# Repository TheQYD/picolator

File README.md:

## Picolator
A portable console for [Pico 8] (http://www.lexaloffle.com/pico-8.php).   

## Details
Picolator is a portable console developed using the Raspberry Pi Zero. It's shell and circuits are made using the [Othermill](https://othermachine.co). 

Anyone with experience in milling and circuit design should be able to make it from just the files. I'll put together an Instructable soon. Check the notes for design details.

## Parts
- 1 [Raspberry Zero] (https://www.adafruit.com/product/2885)
- 1 [Teensy 3.2] (https://www.pjrc.com/store/teensy32.html)
- 1 [Adafruit 3.5” PiTFT] (https://www.adafruit.com/products/2097)
- 1 [LM386 Audio Amplifier] (http://www.digikey.com/product-detail/en/texas-instruments/LM386N-4-NOPB/296-43960-5-ND/148192)
- 1 [Adafruit PowerBoost 500c] (https://www.adafruit.com/product/1944)
- 1 [3.7v 2500mAh LiPo battery] (https://www.adafruit.com/products/328)
- 1 [2.5mm headphone jack] (https://www.amazon.com/uxcell-Plastic-Stereo-Socket-Connector/dp/B00GLQAF7A/ref=pd_sim_23_4/151-6327110-2786334?_encoding=UTF8&pd_rd_i=B00GLQAF7A&pd_rd_r=0DZXJB3YZX57Q64PYSKV&pd_rd_w=IB4NA&pd_rd_wg=bLT86&psc=1&refRID=0DZXJB3YZX57Q64PYSKV)
- 1 [sheet of 4” x 3” x .375” polycarbonate] (https://othermachine.co/store/materials/polycarbonate/)
- 2 [sheets of 4” x 3” x .375” HDPE] (https://othermachine.co/store/materials/hdpe/)
- 1 [sheet of 4” x 3” copper clad FR-1](https://othermachine.co/store/materials/pcb)
- Misc: resistors, capacitors, switch, etc.

## Media
A video it it in action can be found [here](https://youtu.be/5mOcTelc-4U).

The front.

The back.

I use it all the time.

Here are it's insides. I was breadboarding it.

This is the soundboard. It uses an LM386. I designed this circuit for the console, but the Pi Zero audio output instructions can be found [here](https://learn.adafruit.com/introducing-the-raspberry-pi-zero/audio-outputs). It's based on that.

The schematic for the soundboard is in the CADs folder, but here's an image of it.

This is the controller. It connects to the Teensy and the Teensy is then connected via USB to the Pi Zero.

This is a screenshot of the controller circuit. It's also in the CADs folder.

## Notes
The shell is 4 layers. Three HDPE layers and a polycarbonate top layer (to protect the screen). The body was designed in Fusion 360, and the electronics were designed in EagleCAD. All of them were milled using the Othermill. I had to use a Dremel to remove the headers on the PiTFT (risky, but it needed to be thinner). It's not hollow, there are supports and channels to route the wires and mount equipment on the inside (see the CADs).

When I started, I found the PiTFT schematic and tested the pins used for video (SPI). The wires are 28 gauge stranded core. If you look through Google Images for any of those things you'd need, you'll find them. Lady Ada makes the schematics for the PiTFT available on her site. The mappings I found in Google images, and tested using an oscilliscope.

The joystick is milled in two parts. The section for the screen is located in the cads/body directory. The circuit is located in the body/circuits directory. The resistors are 10k pullups. The Teensy code has a mapping of the pins, which are also labeled on the schematic.

The image is Lady Ada's PiTFT image (Raspbian), so the SD Card is 8GB. I couldn't get it booting when I used dd on a 32GB card. If anyone knows why, send me message -- though I don't think that's necessary even if I had every Pico-8 game ever. The games are played in Pico-8. You can place the flags in rc.local so it starts automatically. Pico 8 is available from [Lexaloffle Games](http://www.lexaloffle.com/pico-8.php). All of the games are made by the community using Lua (I guess I'm about to learn Lua!). 

That's it for now, until I have time to write an Instructable.

## License
Picolator is available under the MIT license. See the LICENSE file for more info. Make it better!

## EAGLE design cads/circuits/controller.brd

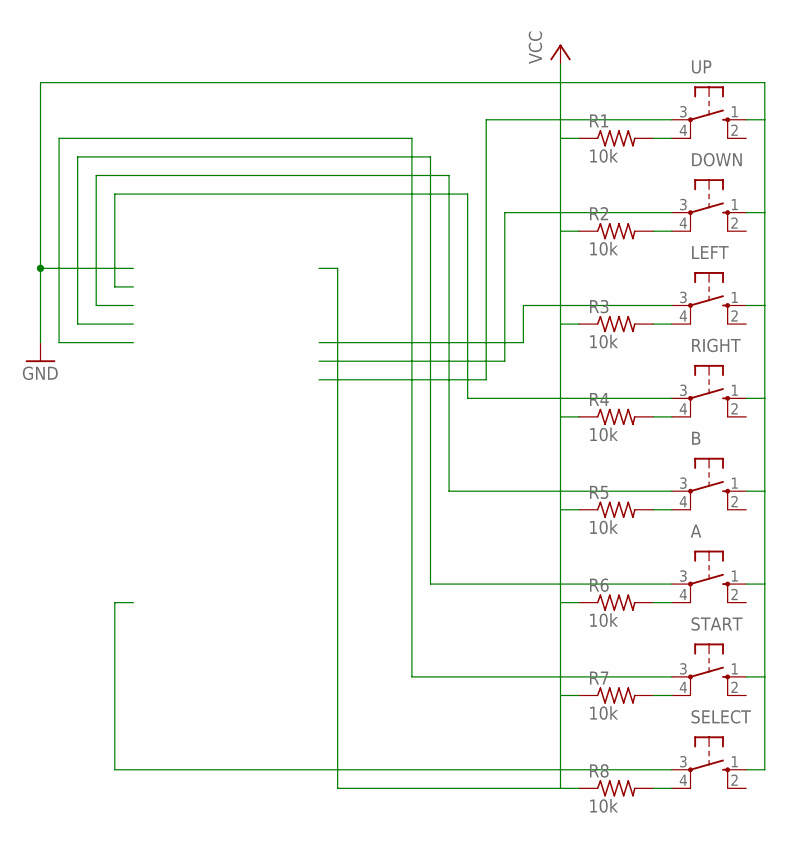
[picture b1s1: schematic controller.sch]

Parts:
A: 10-XX; B3F-10XX
B: 10-XX; B3F-10XX
DOWN: 10-XX; B3F-10XX
LEFT: 10-XX; B3F-10XX
R1, R2, R3, R4, R5, R6, R7, R8: 10k; 0204/7
RIGHT: 10-XX; B3F-10XX
SELECT: 10-XX; B3F-10XX
START: 10-XX; B3F-10XX
UP: 10-XX; B3F-10XX

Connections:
GND: A.1 (S), B.1 (S), DOWN.1 (S), LEFT.1 (S), RIGHT.1 (S), SELECT.1 (S), START.1 (S), UP.1 (S)
unnamed: DOWN.4 (P1), R2.2
unnamed: LEFT.4 (P1), R3.2
unnamed: R1.1, R2.1, R3.1, R4.1, R5.1, R6.1, R7.1, R8.1
unnamed: R7.2, START.4 (P1)
unnamed: R4.2, RIGHT.4 (P1)
unnamed: A.4 (P1), R6.2
unnamed: B.4 (P1), R5.2
unnamed: R8.2, SELECT.4 (P1)
unnamed: R1.2, UP.4 (P1)

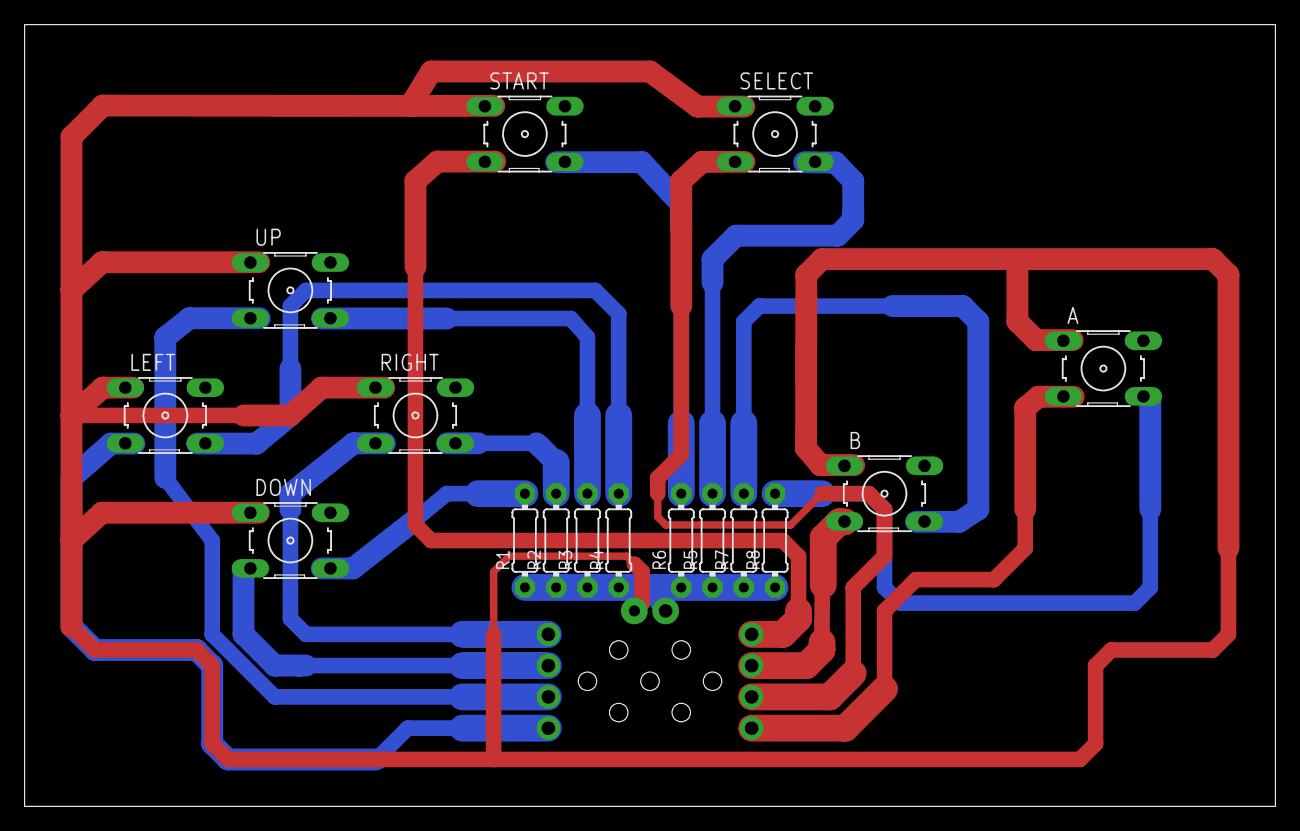
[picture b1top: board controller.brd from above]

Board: 2 copper layers, 101.6 x 63.5 mm, 16 parts (0 on the bottom side), 10 nets.

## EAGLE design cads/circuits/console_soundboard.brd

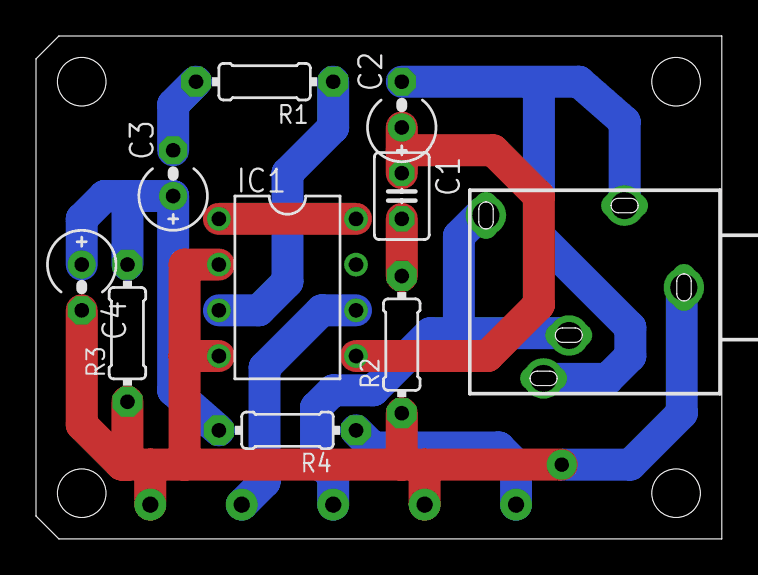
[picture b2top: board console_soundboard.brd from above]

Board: 2 copper layers, 38.1 x 27.9 mm, 10 parts (0 on the bottom side), 9 nets.

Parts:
C1: 47nF; C025-030X050
C2: 220uF; E2,5RE
C3: 10uF; E2,5RE
C4: 33nF; E2,5RE
IC1: LM386N-3; DIL08
R1: 10K; 0204/7
R2: 10R; 0204/7
R3: 150R; 0204/7
R4: 270R; 0204/7
X1: 1503_09

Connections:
unnamed: IC1.3, R1.1
unnamed: C1.1, C2.+, IC1.5
unnamed: C1.2, R2.2
unnamed: C3.+, C4.+, R3.2, R4.2
unnamed: X1.4, X1.5
unnamed: IC1.1, IC1.8
unnamed: C4.-, IC1.2, IC1.4, R2.1, R3.1, X1.1
NN: C3.-, R1.2
OUT: C2.-, X1.2, X1.3

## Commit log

2017-01-04 fixing cads
2017-01-04 Create LICENSE
2017-01-04 Update LICENSE
2021-06-14 Added console soundboard.
